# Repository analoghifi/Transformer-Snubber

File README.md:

# Transformer-Snubber
very effective transformer secondary snubber - without "Rectifier snubbing", the widespread (inaccurate) use of capacitors across the rectifier diodes  

----

Please read the doc:  
"<a href="docs/Quasimodo_jig_revA.pdf">Simple, No-Math Transformer Snubber using “Quasimodo” Test Jig.pdf</a>" by <a href="https://linearaudio.net/authors/436">Mark Johnson</a>  
  
That's what this repo is about:  
Construction of a test jig to determine the correct values for a CRC\* snubber, which fits individually to the measured transformer type, so that no overshoot (=ringing / noise) occurs.  
(see as well this <a href="https://www.diyaudio.com/community/threads/simple-no-math-transformer-snubber-using-quasimodo-test-jig.243100/#post-3645210">forum thread</a> on <a href="https://www.diyaudio.com/community/forums/-/list">diyaudio.com</a> forums)   

----

\*here we use a three element "CRC" snubber on the secondary side of the transformer  
and the exact values for Cx, Rs and Cs (individually for each transformer type) are determined with our "Quasimodo" test jig and an oscilloscope.  

----

see as well this excellent article by <a href="https://linearaudio.net/authors/436">Mark Johnson</a> about the basics and backgrounds of this topic   
"<a href="docs/related/Soft Recovery Diodes Lower Transformer Ringing by 10-20X.pdf">Soft Recovery Diodes Lower Transformer Ringing by 10-20X.pdf</a>"

----

here is also a mathematical approach from TI   
(but for switched-mode power supplies. However, it can also be used for 50/60 Hz applications)  
https://e2e.ti.com/blogs_/b/powerhouse/posts/calculate-an-r-c-snubber-in-seven-steps  
Backup here: <a href="docs/related/Power Tips Calculate an R-C snubber in seven steps.pdf">docs/related/Power Tips Calculate an R-C snubber in seven steps.pdf</a>
  
----  
### Kicad projects in this repo:  
* [quasimodo THT](https://github.com/analoghifi/Transformer-Snubber/tree/main/hardware/KiCad/THT/original) | state: initial release v1.01 | like the original, 2-layer, THT
* [quasimodo SMD](https://github.com/analoghifi/Transformer-Snubber/tree/main/hardware/KiCad/SMD/original) | state: coming soon... | like the original, 2-layer, SMD

----

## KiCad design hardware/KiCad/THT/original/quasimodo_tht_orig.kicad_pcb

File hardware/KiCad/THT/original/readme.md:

these are KiCad 6.x projects  
see how to get the proper 3D-Models from here: https://github.com/analoghifi/KiCad-3D-Models

use kicanvas.org to see this KiCad-Project in your browser:  
https://kicanvas.org/?github=https%3A%2F%2Fgithub.com%2Fanaloghifi%2FTransformer-Snubber%2Ftree%2Fmain%2Fhardware%2FKiCad%2FTHT%2Foriginal

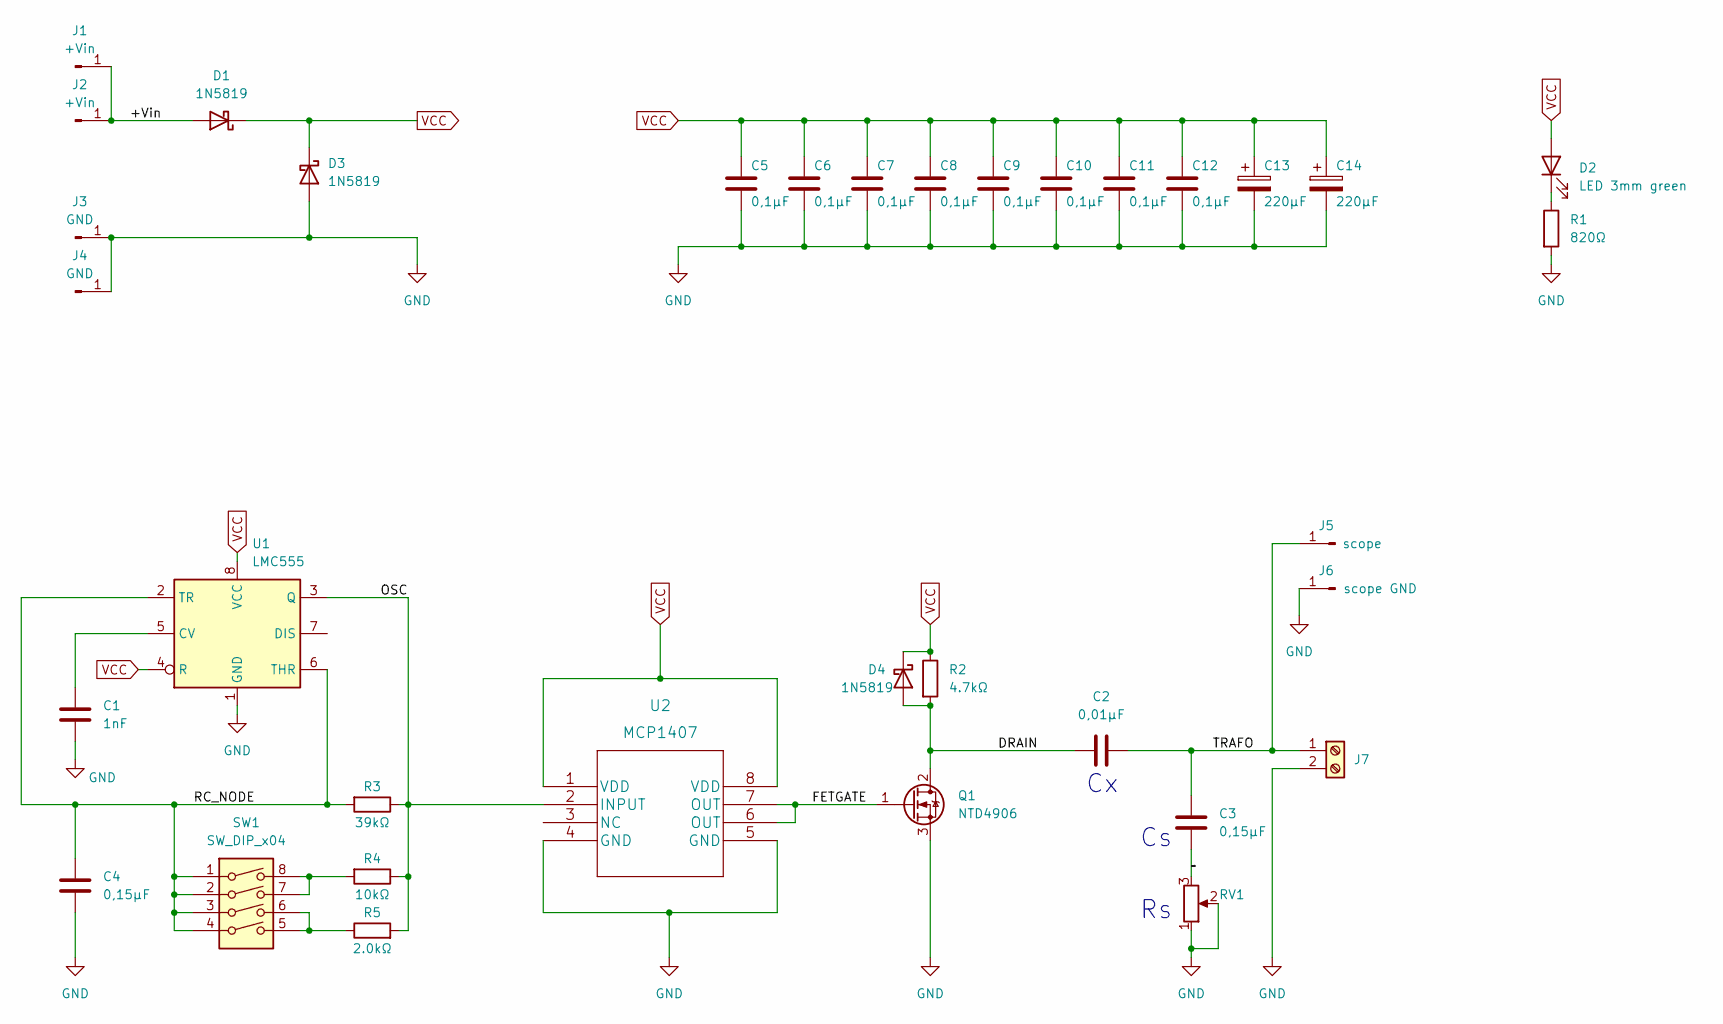
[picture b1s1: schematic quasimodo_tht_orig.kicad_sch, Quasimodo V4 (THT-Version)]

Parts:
C1: 1nF; C_Rect_L7.0mm_W2.5mm_P5.00mm
C2: 0,01µF
C3: 0,15µF
C4: 0,15µF; C_Rect_L7.0mm_W2.5mm_P5.00mm
C5, C6, C7, C8, C9, C10, C11, C12: 0,1µF; C_Rect_L4.6mm_W2.0mm_P2.50mm_MKS02_FKP02
C13, C14: 220µF; CP_Radial_D10.0mm_P5.00mm_medium_silk
D1, D3, D4: 1N5819; D_DO-41_SOD81_P10.16mm_Horizontal
D2: LED 3mm green; LED_D3.0mm
J1, J2: +Vin; PinHeader_1x01_P2.54mm_Vertical
J3, J4: GND; PinHeader_1x01_P2.54mm_Vertical
J5: scope; PinHeader_1x01_P2.54mm_Vertical
J6: scope GND; PinHeader_1x01_P2.54mm_Vertical
J7: Screw_Terminal_01x02; TerminalBlock_Phoenix_PT-1,5-2-5.0-H_1x02_P5.00mm_Horizontal
Q1: NTD4906; TO-220-3_Vertical
R1: 820Ω; R_Axial_DIN0207_L6.3mm_D2.5mm_P10.16mm_Horizontal
R2: 4.7kΩ; R_Axial_DIN0207_L6.3mm_D2.5mm_P10.16mm_Horizontal
R3: 39kΩ; R_Axial_DIN0207_L6.3mm_D2.5mm_P10.16mm_Horizontal
R4: 10kΩ; R_Axial_DIN0207_L6.3mm_D2.5mm_P10.16mm_Horizontal
R5: 2.0kΩ; R_Axial_DIN0207_L6.3mm_D2.5mm_P10.16mm_Horizontal
RV1: Potentiometer_Bourns_3296W_Vertical
SW1: SW_DIP_x04; SW_DIP_SPSTx04_Slide_9.78x12.34mm_W7.62mm_P2.54mm
U1: LMC555; DIP-8_W7.62mm
U2: MCP1407; DIP-8_W7.62mm

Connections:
/+Vin: D1.2 (A), J1.1, J2.1
/DRAIN: C2.1, D4.2 (A), Q1.2 (D), R2.2; also elsewhere on the board
/FETGATE: Q1.1 (G), U2.6 (OUT), U2.7 (OUT)
/OSC: R3.1, R4.1, R5.2, U1.3 (Q), U2.2 (INPUT)
/RC_NODE: C4.1, R3.2, SW1.1, SW1.2, SW1.3, SW1.4, U1.2 (TR), U1.6 (THR)
/TRAFO: C2.2, C3.1, J5.1, J7.1; also elsewhere on the board
GND: C1.2, C4.2, C5.2, C6.2, C7.2, C8.2, C9.2, C10.2, C11.2, C12.2, C13.2, C14.2, D3.2 (A), J3.1, J4.1, J6.1, J7.2, Q1.3 (S), R1.2, RV1.1, RV1.2, U1.1 (GND), U2.4 (GND), U2.5 (GND); also elsewhere on the board
unnamed: C1.1, U1.5 (CV)
unnamed: C3.2, RV1.3
unnamed: D2.1 (K), R1.1
unnamed: R4.2, SW1.7, SW1.8
unnamed: R5.1, SW1.5, SW1.6
VCC: C5.1, C6.1, C7.1, C8.1, C9.1, C10.1, C11.1, C12.1, C13.1, C14.1, D1.1 (K), D2.2 (A), D3.1 (K), D4.1 (K), R2.1, U1.4 (R), U1.8 (VCC), U2.1 (VDD), U2.8 (VDD)

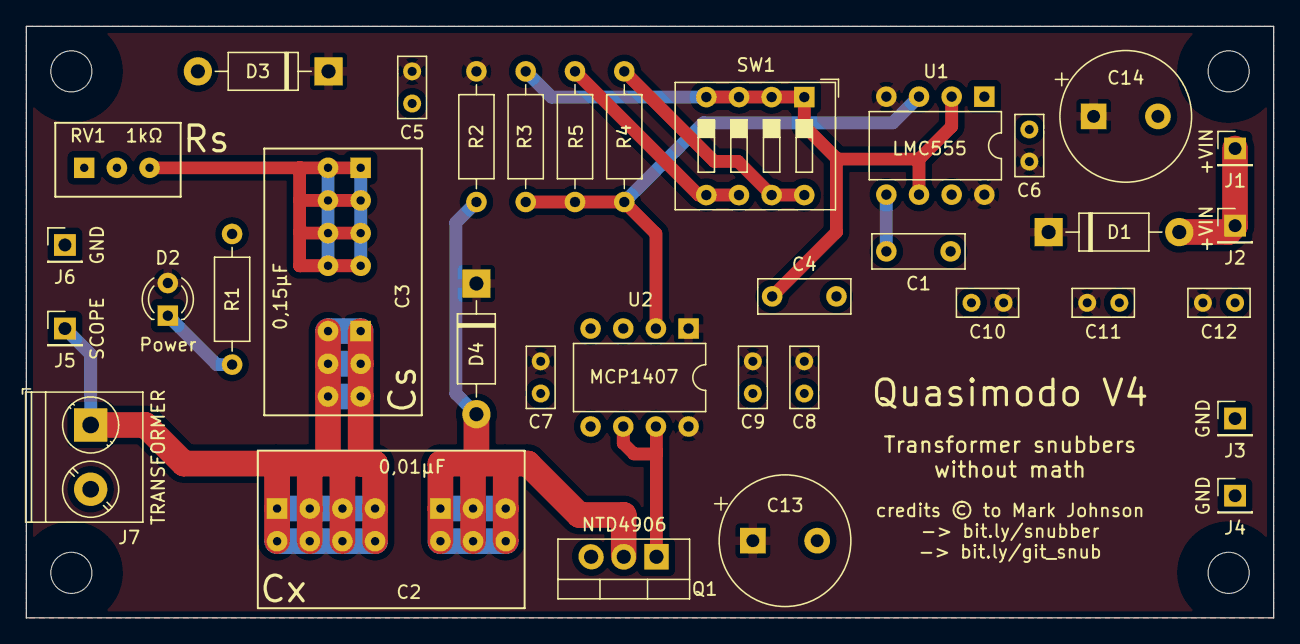
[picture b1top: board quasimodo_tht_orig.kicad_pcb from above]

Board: 2 copper layers, 97.0 x 46.0 mm, 37 parts (0 on the bottom side), 13 nets.

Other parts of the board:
Cs_1: Preci-Dip_2x03_P2.54mm_Vertical_no_silk
Cs_2: Preci-Dip_2x04_P2.54mm_Vertical_no_silk
Cx_1: Preci-Dip_2x03_P2.54mm_Vertical_no_silk
Cx_2: Preci-Dip_2x04_P2.54mm_Vertical_no_silk
Rs: Preci-Dip_1x03_P2.54mm_Vertical_no_silk

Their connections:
/DRAIN: Cx_1.1, Cx_1.2, Cx_1.3, Cx_1.4, Cx_1.5, Cx_1.6; also elsewhere on the board
/TRAFO: Cs_1.1, Cs_1.2, Cs_1.3, Cs_1.4, Cs_1.5, Cs_1.6, Cx_2.1, Cx_2.2, Cx_2.3, Cx_2.4, Cx_2.5, Cx_2.6, Cx_2.7, Cx_2.8; also elsewhere on the board
GND: Rs.1, Rs.2; also elsewhere on the board
Rs_Cs: Cs_2.1, Cs_2.2, Cs_2.3, Cs_2.4, Cs_2.5, Cs_2.6, Cs_2.7, Cs_2.8, Rs.3

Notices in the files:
hardware/KiCad/THT/original/quasimodo_tht_orig.kicad_pcb:
credits © to Mark Johnson
